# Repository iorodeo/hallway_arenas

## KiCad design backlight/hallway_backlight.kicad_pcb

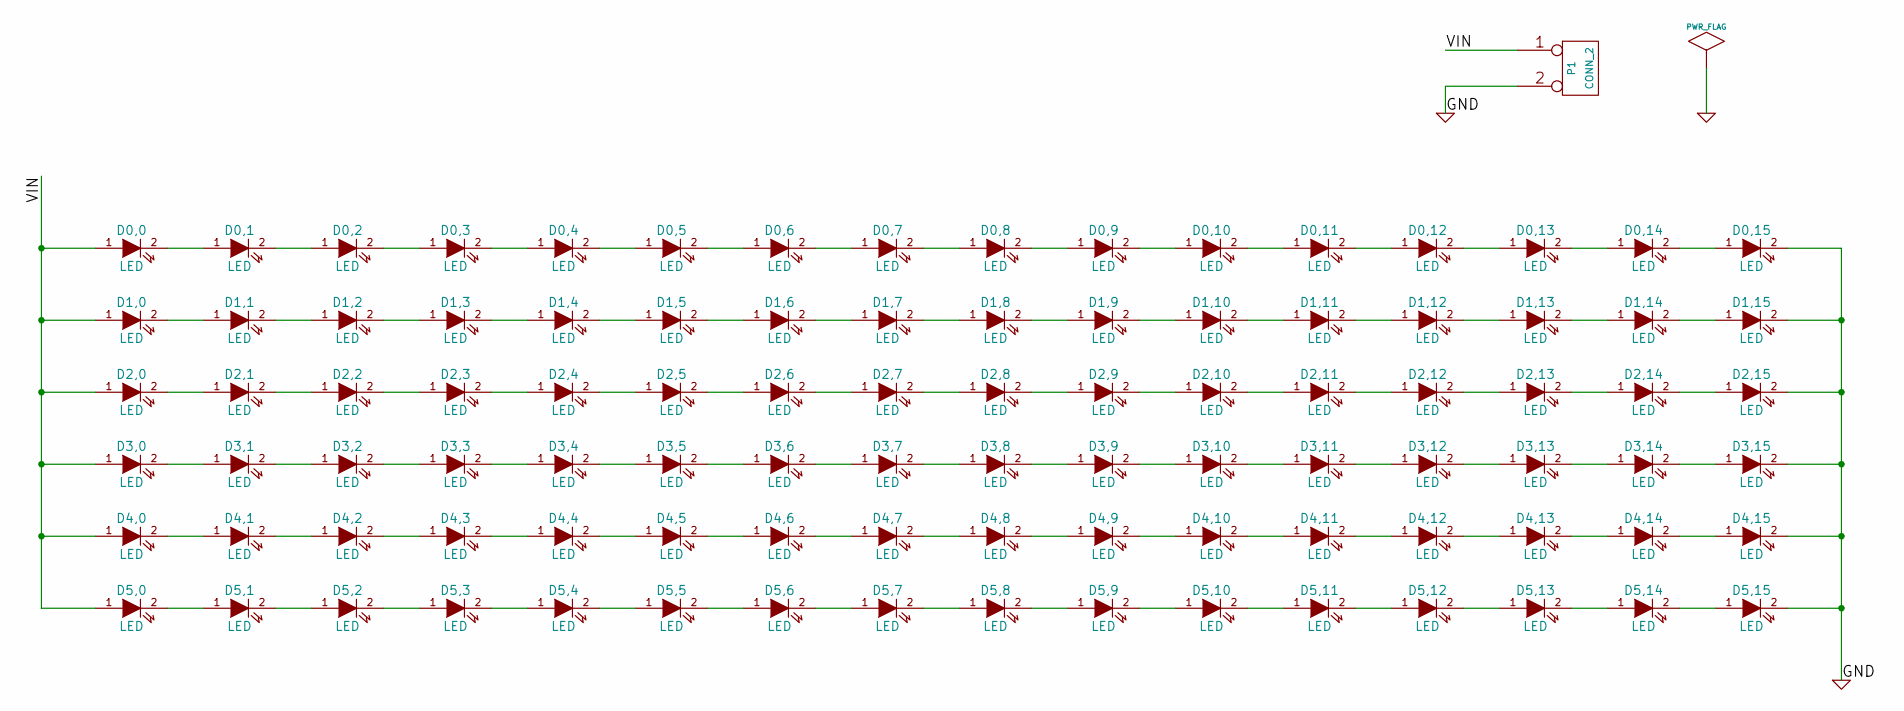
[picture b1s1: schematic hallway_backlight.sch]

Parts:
D0,0, D0,1, D0,2, D0,3, D0,4, D0,5, D0,6, D0,7, D0,8, D0,9, D0,10, D0,11, D0,12, D0,13, D0,14, D0,15, D1,0, D1,1, D1,2, D1,3, D1,4, D1,5, D1,6, D1,7, D1,8, D1,9, D1,10, D1,11, D1,12, D1,13, D1,14, D1,15, D2,0, D2,1, D2,2, D2,3, D2,4, D2,5, D2,6, D2,7, D2,8, D2,9, D2,10, D2,11, D2,12, D2,13, D2,14, D2,15, D3,0, D3,1, D3,2, D3,3, D3,4, D3,5, D3,6, D3,7, D3,8, D3,9, D3,10, D3,11, D3,12, D3,13, D3,14, D3,15, D4,0, D4,1, D4,2, D4,3, D4,4, D4,5, D4,6, D4,7, D4,8, D4,9, D4,10, D4,11, D4,12, D4,13, D4,14, D4,15, D5,0, D5,1, D5,2, D5,3, D5,4, D5,5, D5,6, D5,7, D5,8, D5,9, D5,10, D5,11, D5,12, D5,13, D5,14, D5,15: LED
P1: CONN_2

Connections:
/VIN: D0,0.1 (A), D1,0.1 (A), D2,0.1 (A), D3,0.1 (A), D4,0.1 (A), D5,0.1 (A), P1.1
GND: D0,15.2 (K), D1,15.2 (K), D2,15.2 (K), D3,15.2 (K), D4,15.2 (K), D5,15.2 (K), P1.2 (PM)
unnamed: D5,14.2 (K), D5,15.1 (A)
unnamed: D5,13.2 (K), D5,14.1 (A)
unnamed: D5,12.2 (K), D5,13.1 (A)
unnamed: D5,11.2 (K), D5,12.1 (A)
unnamed: D5,10.2 (K), D5,11.1 (A)
unnamed: D5,9.2 (K), D5,10.1 (A)
unnamed: D5,8.2 (K), D5,9.1 (A)
unnamed: D5,7.2 (K), D5,8.1 (A)
unnamed: D5,6.2 (K), D5,7.1 (A)
unnamed: D5,5.2 (K), D5,6.1 (A)
unnamed: D5,4.2 (K), D5,5.1 (A)
unnamed: D5,3.2 (K), D5,4.1 (A)
unnamed: D5,2.2 (K), D5,3.1 (A)
unnamed: D5,1.2 (K), D5,2.1 (A)
unnamed: D5,0.2 (K), D5,1.1 (A)
unnamed: D4,14.2 (K), D4,15.1 (A)
unnamed: D4,13.2 (K), D4,14.1 (A)
unnamed: D4,12.2 (K), D4,13.1 (A)
unnamed: D4,11.2 (K), D4,12.1 (A)
unnamed: D4,10.2 (K), D4,11.1 (A)
unnamed: D4,9.2 (K), D4,10.1 (A)
unnamed: D4,8.2 (K), D4,9.1 (A)
unnamed: D4,7.2 (K), D4,8.1 (A)
unnamed: D4,6.2 (K), D4,7.1 (A)
unnamed: D4,5.2 (K), D4,6.1 (A)
unnamed: D4,4.2 (K), D4,5.1 (A)
unnamed: D4,3.2 (K), D4,4.1 (A)
unnamed: D4,2.2 (K), D4,3.1 (A)
unnamed: D4,1.2 (K), D4,2.1 (A)
unnamed: D4,0.2 (K), D4,1.1 (A)
unnamed: D3,14.2 (K), D3,15.1 (A)
unnamed: D3,13.2 (K), D3,14.1 (A)
unnamed: D3,12.2 (K), D3,13.1 (A)
unnamed: D3,11.2 (K), D3,12.1 (A)
unnamed: D3,10.2 (K), D3,11.1 (A)
unnamed: D3,9.2 (K), D3,10.1 (A)
unnamed: D3,8.2 (K), D3,9.1 (A)
unnamed: D3,7.2 (K), D3,8.1 (A)
unnamed: D3,6.2 (K), D3,7.1 (A)
unnamed: D3,5.2 (K), D3,6.1 (A)
unnamed: D3,4.2 (K), D3,5.1 (A)
unnamed: D3,3.2 (K), D3,4.1 (A)
unnamed: D3,2.2 (K), D3,3.1 (A)
unnamed: D3,1.2 (K), D3,2.1 (A)
unnamed: D3,0.2 (K), D3,1.1 (A)
unnamed: D2,14.2 (K), D2,15.1 (A)
unnamed: D2,13.2 (K), D2,14.1 (A)
unnamed: D2,12.2 (K), D2,13.1 (A)
unnamed: D2,11.2 (K), D2,12.1 (A)
unnamed: D2,10.2 (K), D2,11.1 (A)
unnamed: D2,9.2 (K), D2,10.1 (A)
unnamed: D2,8.2 (K), D2,9.1 (A)
unnamed: D2,7.2 (K), D2,8.1 (A)
unnamed: D2,6.2 (K), D2,7.1 (A)
unnamed: D2,5.2 (K), D2,6.1 (A)
unnamed: D2,4.2 (K), D2,5.1 (A)
unnamed: D2,3.2 (K), D2,4.1 (A)
unnamed: D2,2.2 (K), D2,3.1 (A)
unnamed: D2,1.2 (K), D2,2.1 (A)
unnamed: D2,0.2 (K), D2,1.1 (A)
unnamed: D1,14.2 (K), D1,15.1 (A)
unnamed: D1,13.2 (K), D1,14.1 (A)
unnamed: D1,12.2 (K), D1,13.1 (A)
unnamed: D1,11.2 (K), D1,12.1 (A)
unnamed: D1,10.2 (K), D1,11.1 (A)
unnamed: D1,9.2 (K), D1,10.1 (A)
unnamed: D1,8.2 (K), D1,9.1 (A)
unnamed: D1,7.2 (K), D1,8.1 (A)
unnamed: D1,6.2 (K), D1,7.1 (A)
unnamed: D1,5.2 (K), D1,6.1 (A)
unnamed: D1,4.2 (K), D1,5.1 (A)
unnamed: D1,3.2 (K), D1,4.1 (A)
unnamed: D1,2.2 (K), D1,3.1 (A)
unnamed: D1,1.2 (K), D1,2.1 (A)
unnamed: D1,0.2 (K), D1,1.1 (A)
unnamed: D0,14.2 (K), D0,15.1 (A)
unnamed: D0,13.2 (K), D0,14.1 (A)
unnamed: D0,12.2 (K), D0,13.1 (A)
unnamed: D0,11.2 (K), D0,12.1 (A)
unnamed: D0,10.2 (K), D0,11.1 (A)
unnamed: D0,9.2 (K), D0,10.1 (A)
unnamed: D0,8.2 (K), D0,9.1 (A)
unnamed: D0,7.2 (K), D0,8.1 (A)
unnamed: D0,6.2 (K), D0,7.1 (A)
unnamed: D0,5.2 (K), D0,6.1 (A)
unnamed: D0,4.2 (K), D0,5.1 (A)
unnamed: D0,3.2 (K), D0,4.1 (A)
unnamed: D0,2.2 (K), D0,3.1 (A)
unnamed: D0,1.2 (K), D0,2.1 (A)
unnamed: D0,0.2 (K), D0,1.1 (A)

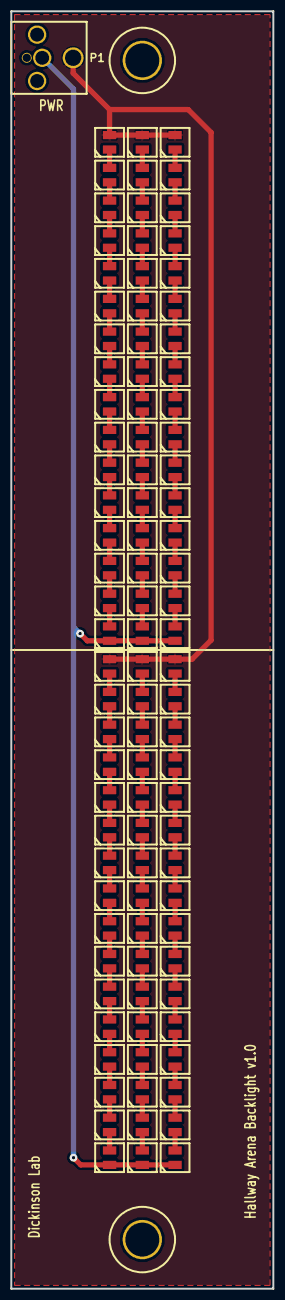
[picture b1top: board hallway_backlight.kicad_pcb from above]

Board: 2 copper layers, 50.8 x 247.6 mm, 99 parts (0 on the bottom side), 92 nets.

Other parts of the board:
1/4-20, 1/4-20#2: VAL**; 1%2f4-20

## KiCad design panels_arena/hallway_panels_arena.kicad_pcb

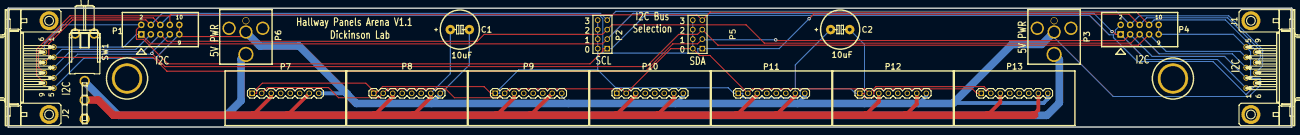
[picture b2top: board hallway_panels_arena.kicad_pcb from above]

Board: 2 copper layers, 342.9 x 31.8 mm, 20 parts (0 on the bottom side), 13 nets.

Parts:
1/4-20,1, 1/4-20,2: VAL**; 1%2f4-20
C1, C2: 10uF; JFRC_Capacitor_Polarized
J1, J2: DB9; DB9_M09
P1, P4: CONN_5X2; HEADER_5x2_LARGE
P2, P5: CONN_4X2; pin_array_4x2
P3, P6: CONN_2; DCJACK_2PIN_HIGHCURRENT
P7, P8, P9, P10, P11, P12, P13: CONN_8; JFRC_1X08
SW1: SWITCH_INV; JFRC_LPV-1

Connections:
/5V: C1.1, C2.1, P7.3, P7.7, P8.3, P8.7, P9.3, P9.7, P10.3, P10.7, P11.3, P11.7, P12.3, P12.7, P13.3, P13.7, SW1.2
/SCL: P2.2, P2.4, P2.6, P2.8, P7.1, P8.1, P9.1, P10.1, P11.1, P12.1, P13.1
/SCL0: J1.6, J2.6, P1.2, P2.1, P4.2
/SCL1: J1.1, J2.1, P1.1, P2.3, P4.1
/SCL2: J1.3, J2.3, P1.5, P2.5, P4.5
/SCL3: J1.7, J2.7, P1.4, P2.7, P4.4
/SDA: P5.2, P5.4, P5.6, P5.8, P7.2, P8.2, P9.2, P10.2, P11.2, P12.2, P13.2
/SDA0: J1.8, J2.8, P1.6, P4.6, P5.1
/SDA1: J1.2, J2.2, P1.3, P4.3, P5.3
/SDA2: J1.4, J2.4, P1.7, P4.7, P5.5
/SDA3: J1.9, J2.9, P1.8, P4.8, P5.7
GND: C1.2, C2.2, J1.5, J2.5, P1.9, P1.10, P3.2, P4.9, P4.10, P6.2, P7.8, P8.8, P9.8, P10.8, P11.8, P12.8, P13.8
unnamed: P3.1, P6.1, SW1.1

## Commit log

2011-07-05 Project creation.
2011-07-05 Added license.
2011-07-05 Added panels, panels pcb, headers. Modified assembly class so that translations and rotations are applied to individual objects.
2011-07-05 Modified assembly files and part class so that rotations, translations and color commands are handled differently.
2011-07-05 Added stl file creation for system assembly.
2011-07-06 Added vconfig creation for stl file version of assemblies.
2011-07-19 Changed backlight color.
2011-07-20 Add breadboard model, build script. Modified backlight standoffs so that they are on vibration grommets. Modofied Standoff_Grommet_Assembly so that the name of the standoff parameters can be specifie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
2011-07-21 Added two arena assembly and pager motor holder.
2011-07-21 Removed cutouts for pager motors. Added pager motor holders to arena assemblies.
2011-07-21 Added camera posts, camera plate, camera model.
2011-07-22 Added bracket and stl creation file for breadboard (because it takes a long time). Moved stl create to the Part class.
2011-07-25 Uncommented breadboard holes.
2011-07-25 Put mechanical design in directory named "mechanics".
2011-07-26 Finished design of backlight pcb.
2011-07-27 Finished hallway panels arena design. Still need to add annotation to the board.
2011-07-27 Added licenses.
2011-08-10 Finished initial design.
2011-08-10 Added version 1 of the gerber file for the linear arena and the backlight. These are the versions ordered from PCB manufacturer.
2011-08-11 Worked on bill-of-material for mechanics. Resized some of the standoffs due to availability.
2011-08-11 Worked some more on bill of materials.
2011-08-16 Added BOMs.
2011-08-16 Created version 1.0 version of dxf files for laser cutting.
2011-08-16 Added dxf
    Added camera plate dxf file.
2011-09-14 Created enclosure for nano solid state relay board.
2015-05-21 Added pdf version of diffuser design.
2015-05-28 Added in version of diffuser dxf.
2020-04-21 Upgraded hallway arena for kicad 4
2020-04-21 update backligh for kicad 4.
2020-04-21 Added a version of PCBs with Dickinson Lab on them instead of IO Rodeo.
